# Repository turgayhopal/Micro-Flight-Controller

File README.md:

# Micro Flight Controller

- This project developed for micro drone.

### Board Features

- STM32F422RET6 Microcontroller
- 1A Buck-Boost Converter (TPS63031)
- CRSF Port (like RadioMaster RP1)
- 128 KB External Flash
- MS5611 Barometer
- MPU6500 Sensor

### PCB Features

- 35.1mm x 34.1mm
- 1mm board thickness.
- 4 layer PCB.
- 0.45 / 0.3 vias

### Right Side

### Front Side

### Back Side

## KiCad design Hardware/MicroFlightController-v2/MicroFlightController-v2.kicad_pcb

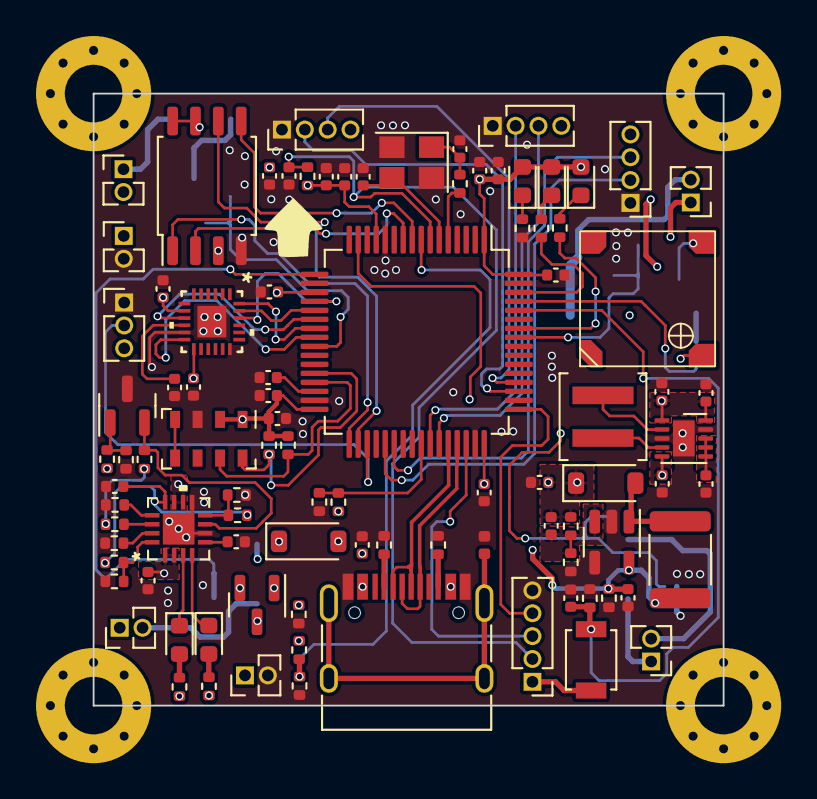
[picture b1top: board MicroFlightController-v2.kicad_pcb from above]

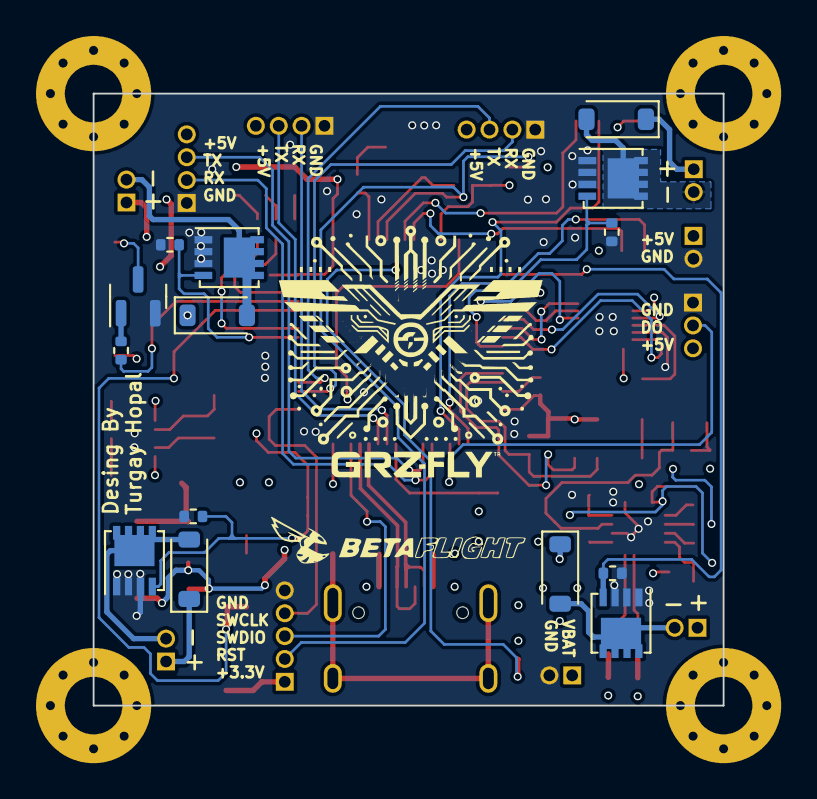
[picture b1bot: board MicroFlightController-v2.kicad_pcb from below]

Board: 4 copper layers, 35.0 x 34.0 mm, 107 parts (14 on the bottom side), 74 nets.

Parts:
C1, C3, C5, C6, C8, C9, C10, C14, C15, C16, C18, C19, C22: 100nF; C_0402_1005Metric
C2, C28: 1uF; C_0402_1005Metric
C4, C7: 22pF; C_0402_1005Metric
C11, C20: 2.2uF; C_0402_1005Metric
C12, C13, C21, C24, C25: 10uF; C_0402_1005Metric
C17, C27: 10nF; C_0402_1005Metric
C23: 220pF; C_0402_1005Metric
C26: 4.7uF; C_0402_1005Metric
C29: 1nF; C_0402_1005Metric
D1, D2: MBR0520; D_SOD-123
D3, D4, D5, D6, D7: LED; LED_0603_1608Metric
D8, D9, D10, D11: MBR0560; D_SOD-123
J1: USB_C_Receptacle_USB2.0; USB_C_Receptacle_HRO_TYPE-C-31-M-12
J2: Debug; PinHeader_1x05_P1.27mm_Vertical
J3: VBAT; PinHeader_1x02_P1.27mm_Vertical
J4: Conn_01x03_Pin; PinHeader_1x03_P1.27mm_Vertical
J5: Conn_01x02_Pin; PinHeader_1x02_P1.27mm_Vertical
J6, J8: UART; PinHeader_1x04_P1.27mm_Vertical
J7: Radio Master RP1 Receiver; PinHeader_1x04_P1.27mm_Vertical
J9: ENGINE-1; PinHeader_1x02_P1.27mm_Vertical
J10: ENGINE-2; PinHeader_1x02_P1.27mm_Vertical
J11: ENGINE-3; PinHeader_1x02_P1.27mm_Vertical
J12: ENGINE-4; PinHeader_1x02_P1.27mm_Vertical
L1: 220R; L_0402_1005Metric
L2: 1.5uH; L_Coilcraft_XAL4020-XXX
L3: 10uH; L_1812_4532Metric
Q1: IRLM2803; SOT-23
Q2: IRLML5203; SOT-23
Q3: MMBT3904; SOT-23
Q4, Q5, Q6, Q7: SiS454DN; Vishay_PowerPAK_1212-8_Single
R1, R3, R8, R9, R10, R25, R26, R27, R32, R33, R34, R35: 10K; R_0402_1005Metric
R2, R4: 5.1K; R_0402_1005Metric
R5: 15K; R_0402_1005Metric
R6: 22K; R_0402_1005Metric
R7: 220R; R_0402_1005Metric
R11, R16, R22, R23, R24, R29, R30, R31: 1K; R_0402_1005Metric
R12: 100K; R_0402_1005Metric
R13: 47K; R_0402_1005Metric
R14: 13.3K; R_0402_1005Metric
R15: 40.7K; R_0402_1005Metric
R17: 3.3K; R_0402_1005Metric
R18: 470R; R_0402_1005Metric
R19: 24K; R_0402_1005Metric
R20: 39K; R_0402_1005Metric
R21: 62K; R_0402_1005Metric
R28: 120R; R_0402_1005Metric
SW1: RESET; SW_SPST_B3U-1000P
U1: STM32F722RETx; LQFP-64_10x10mm_P0.5mm
U2: TPS63031DSK; WSON-10-1EP_2.5x2.5mm_P0.5mm_EP1.2x2mm
U3: MS5611-01BA; LGA-8_3x5mm_P1.25mm
U4: W25Q128JVS; SOIC-8_5.23x5.23mm_P1.27mm
U5: LMR62014XMF; SOT-23-5
U7: L6924D013TR
U8: YX7527P
U9: MPU-6500; QFN24_3X3X0P9_IVS
Y1: 16MHz; Crystal_SMD_3225-4Pin_3.2x2.5mm

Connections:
+3.3V: C5.2, C6.2, C8.2, C9.2, C10.2, C12.2, C13.2, C14.2, C15.2, C17.2, C18.1, C19.1, C20.1, C24.1, C25.1, D5.2 (A), D6.2 (A), D7.2 (A), J2.1, L3.1, R1.1, R8.1, R9.1, R13.1, R25.1, R27.1, SW1.1, U1.1 (VBAT), U1.13 (VDDA), U1.19 (VDD), U1.32 (VDD), U1.48 (VDD), U1.64 (VDD), U2.1 (VOUT), U2.10 (FB), U3.1 (VDD), U3.2 (PS), U4.3 (IO2), U4.7 (IO3), U4.8 (VCC), U5.5 (VIN), U8.1 (VDD), U9.8 (VDDIO), U9.13 (VDD)
+5V: C23.2, C26.2, D2.1 (K), J4.3, J5.1, J6.4, J7.4, J8.4, R15.2
/Baro/SCL: R9.2, U1.28 (PB10), U3.8 (SCLK)
/Baro/SDA: R8.2, U1.29 (PB11), U3.7 (SDI/SDA)
/Battery Charger/IPRE: R20.2, R21.1, U7.16 (IPRE)
/Battery Charger/SD: Q2.2 (S), R27.2, U7.7 (SD)
/Battery Charger/TH: R16.1, R18.1, U7.8 (TH)
/Battery Charger/VPRE: R25.2, U7.14 (VPRE)
/Battery Charger/VREF: C29.1, R16.2, R20.1, U7.12 (VREF)
/Buck Boost Converter/VBAT-MESAURE: R10.2, R11.1, U1.8 (PC0)
/Flash/CLK: U1.34 (PB13), U4.6 (CLK)
/Flash/CS: U1.33 (PB12), U4.1 (~CS)
/Flash/MISO: U1.10 (PC2), U4.2 (DO(IO1))
/Flash/MOSI: U1.9 (PC1), U4.5 (DI(IO0))
/MCU/BOOT0: C3.1, R3.2, SW1.2, U1.60 (BOOT0)
/MCU/NRST: C1.1, J2.2, R1.2, U1.7 (NRST)
/MCU/PA1: Q5.4 (G), R33.1, U1.15 (PA1)
/MCU/PA3: Q4.4 (G), R32.1, U1.17 (PA3)
/MCU/PA4: U1.20 (PA4), U9.22 (nCS)
/MCU/PA5: U1.21 (PA5), U9.23 (SCL/SCLK)
/MCU/PA6: U1.22 (PA6), U9.9 (SDO/ADO)
/MCU/PA7: U1.23 (PA7), U9.24 (SDA/SDI)
/MCU/PA9: J7.2, U1.42 (PA9)
/MCU/PA10: J7.3, U1.43 (PA10)
/MCU/PB0: Q6.4 (G), R34.1, U1.25 (PB0)
/MCU/PB5: Q7.4 (G), R35.1, U1.57 (PB5)
/MCU/PB6: R31.2, U1.58 (PB6)
/MCU/PB8: R28.1, U1.61 (PB8)
/MCU/PB9: R30.2, U1.62 (PB9)
/MCU/PB14: J4.2, U1.35 (PB14)
/MCU/PC4: U1.24 (PC4), U9.12 (INT)
/MCU/PC6: J8.2, U1.37 (PC6)
/MCU/PC7: J8.3, U1.38 (PC7)
/MCU/PC10: J6.2, U1.51 (PC10)
/MCU/PC11: J6.3, U1.52 (PC11)
/MCU/SWCLK: J2.4, U1.49 (PA14)
/MCU/SWDIO: J2.3, U1.46 (PA13)
/MCU/USB_D+: J1.A6 (D+), J1.B6 (D+), U1.45 (PA12)
/MCU/USB_D-: J1.A7 (D-), J1.B7 (D-), U1.44 (PA11)
/MCU/VBUS_DETECT: R5.2, R6.1, U1.41 (PA8)
/MCU/X_IN: R7.1, U1.5 (PH0)
/MCU/X_OUT: C7.1, U1.6 (PH1), Y1.3
GND: C1.2, C2.1, C3.2, C4.2, C5.1, C6.1, C7.2, C8.1, C9.1, C10.1, C11.2, C12.1, C13.1, C14.1, C15.1, C16.1, C17.1, C18.2, C19.2, C20.2, C21.2, C22.1, C24.2, C25.2, C26.1, C27.2, C28.2, C29.2, J1.A1 (GND), J1.A12 (GND), J1.B1 (GND), J1.B12 (GND), J2.5, J3.2, J4.1, J5.2, J6.1, J7.1, J8.1, L1.2, Q2.3 (D), Q3.2 (E), Q4.1 (S), Q4.2 (S), Q4.3 (S), Q5.1 (S), Q5.2 (S), Q5.3 (S), Q6.1 (S), Q6.2 (S), Q6.3 (S), Q7.1 (S), Q7.2 (S), Q7.3 (S), R2.2, R3.1, R4.2, R6.2, R11.2, R12.1, R13.2, R14.2, R17.2, R18.2, R19.2, R21.2, R26.1, R29.2, R32.2, R33.2, R34.2, R35.2, U1.12 (VSSA), U1.18 (VSS), U1.31 (VSS), U1.47 (VSS), U1.63 (VSS), U2.3 (PGND), U2.9 (GND), U2.11 (PGND), U3.3 (GND), U4.4 (GND), U5.2 (GND), U5.4 (EN), U7.6 (GND), U7.9 (VOPRG), U7.17, U9.11 (FSYNC), U9.18 (GND), U9.25, Y1.2, Y1.4
unnamed: C4.1, R7.2, Y1.1
unnamed: D2.2 (A), L3.2, U5.1 (SW)
unnamed: D3.2 (A), R22.1
unnamed: D3.1 (K), U7.4 (ST1)
unnamed: D4.2 (A), R23.1
unnamed: D4.1 (K), U7.3 (ST2)
unnamed: D5.1 (K), R29.1
unnamed: D6.1 (K), R30.1
unnamed: D7.1 (K), R31.1
unnamed: D8.2 (A), J9.2, Q4.5 (D)
unnamed: D9.2 (A), J10.2, Q5.5 (D)
unnamed: D10.2 (A), J11.2, Q6.5 (D)
unnamed: D11.2 (A), J12.2, Q7.5 (D)
unnamed: J1.A5 (CC1), R2.1
unnamed: J1.B5 (CC2), R4.1
unnamed: J1.S1 (SHIELD), L1.1
unnamed: Q2.1 (G), R24.1, R26.2
unnamed: Q3.1 (B), R28.2
unnamed: Q3.3 (C), U8.2 (VSS)
unnamed: C11.1, U1.30 (VCAP_1)
unnamed: C22.2, U2.6 (EN), U2.7 (PS/SYNC), U2.8 (VINA)
unnamed: L2.2, U2.4 (L1)
unnamed: L2.1, U2.2 (L2)
unnamed: C23.1, R14.1, R15.1, U5.3 (FB)
unnamed: R17.1, U7.13 (IEND)
unnamed: R19.1, U7.15 (IPRG)
unnamed: C27.1, U7.5 (TPRG)
unnamed: C16.2, U9.10 (REGOUT)
VBAT: D8.1 (K), D9.1 (K), D10.1 (K), D11.1 (K), J3.1, J9.1, J10.1, J11.1, J12.1, Q1.3 (D), R10.1, U7.10 (VOSNS), U7.11 (VOUT)
VBUS: C2.2, C28.1, D1.2 (A), J1.A4 (VBUS), J1.A9 (VBUS), J1.B4 (VBUS), J1.B9 (VBUS), Q1.1 (G), R5.1, R12.2, R22.2, R23.2, R24.2, U7.1 (VIN), U7.2 (VINSNS)
VIN: C21.1, D1.1 (K), Q1.2 (S), U2.5 (VIN)

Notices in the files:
parts and their libraries:
Copyright 2021 Accelerated Designs. All rights reserved.
